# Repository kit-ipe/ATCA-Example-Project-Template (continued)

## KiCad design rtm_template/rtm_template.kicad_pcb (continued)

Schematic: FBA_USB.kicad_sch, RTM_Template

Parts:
C20: 100nF; C_0603_1608Metric; voltage 16 V
C23, C27, C29, C31: 10uF; C_1210_3225Metric; voltage 25 V; digikey# 445-3942-1-ND
C25, C28: 1uF; C_0402_1005Metric; voltage 16 V
C26, C30, C32, C35, C36, C41, C42, C43, C44, C45, C46, C47, C48, C49, C50, C51, C53, C54, C55: 100nF; C_0402_1005Metric; voltage 16 V
C33: 100nF; C_0402_1005Metric
C34, C37: 27pF; C_0402_1005Metric; voltage 50 V; digikey# 587-3745-1-ND
C38, C39, C40: 4.7uF; C_0603_1608Metric; voltage 25 V
FB1, FB2, FB3: 220 @ 100MHz; L_0603_1608Metric; digikey# 490-5225-1-ND
J8: USB_B_Micro; USB_Micro-B_Molex_47346-0001; digikey# WM17141CT-ND
J12: Conn_02x05_Odd_Even; IDC-Header_2x05_P2.54mm_Horizontal_withoutsilkscreen; mouser# 571-5103311-1; digikey# A33180-ND
R40: 1M; R_0603_1608Metric
R42, R44, R46, R48, R65, R68: 4k7; R_0402_1005Metric; tolerance 1%; digikey# A129635CT-ND
R57, R60: 33; R_0402_1005Metric; digikey# A129609CT-ND
R61, R63, R64, R70: 10k; R_0402_1005Metric; tolerance 1%; digikey# A129639CT-ND
R62, R71: 2k; R_0402_1005Metric; tolerance 1%; digikey# RMCF0402FT2K00CT-ND
R66: 12k; R_0402_1005Metric; tolerance 1%; digikey# A129640CT-ND
R67, R72: 1k; R_0402_1005Metric; tolerance 1%; digikey# A129627CT-ND
R69: DNP; R_0402_1005Metric_DNP
U8: AZ1117-3.3; SOT-223-3_TabPin2; mouser# 621-AZ1117CH-3.3TRG1; digikey# AZ1117CH-3.3TRG1DICT-ND
U9: MIC94161YCS-TR; WLCSP-6_1.0x1.5mm_P0.5mm; mouser# 998-MIC94161YCS-TR; digikey# 576-4453-1-ND
U10: USBLC6-4SC6; SOT-23-6; mouser# 511-USBLC6-4SC6Y; digikey# 497-11883-1-ND
U11: 93LC56B-MC; DFN-8-1EP_3x2mm_P0.5mm_EP1.75x1.45mm; mouser# 579-93LC56BT-I/MC; digikey# 93LC56BT-I/MCCT-ND
U12: FT4232H-56Q; VQFN-56-1EP_8x8mm_P0.5mm_EP5.9x5.9mm; mouser# 895-FT4232H-56Q-TRAY; digikey# 768-1378-1-ND
U13: TXS0104RGYR; Texas_S-PVQFN-N14; mouser# 595-TXS0104ERGYR; digikey# 296-20698-1-ND
U14: MAX9100EUK-T; SOT-23-5; mouser# 700-MAX9100EUKT; digikey# MAX9100EUK+TCT-ND
U15: SN74LVC07APW; TSSOP-14_4.4x5mm_P0.65mm; digikey# 296-26575-5-ND
Y1: ECS-120-12-36Q-CWY-TR; Crystal_SMD_2520-4Pin_2.5x2.0mm; mouser# 520-120-12-36Q-CWYT; digikey# XC2419CT-ND

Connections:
+1V8_USB_VCORE: C35.1, C36.1, C40.1, C43.1, C46.1, C48.1, U12.2 (VCORE), U12.31 (VCORE), U12.43 (VREGOUT)
+3V3_USB_VCCIO: C29.1, C32.1, C44.1, C47.1, C49.1, C50.1, C51.1, C55.1, FB2.2, FB3.2, R61.1, R63.1, R64.1, R67.2, R69.1, R71.2, U8.2 (VO), U11.8 (VCC), U12.16 (VCCIO), U12.36 (VCCIO), U12.44 (VREGIN), U12.50 (VCCIO), U13.14 (VCCB), U14.5 (V+)
+5V_USB_VBUS: C27.1, C28.1, C30.1, FB1.1, U8.3 (VI)
/FBA_USB/3V3_FT_INT: C31.1, J12.4, R42.1, R44.1, R46.1, R48.1, R65.1, U9.A1 (VOUT), U9.B1 (VOUT)
/FBA_USB/EECLK: R63.2, U11.2 (SCLK), U12.56 (EECLK)
/FBA_USB/EECS: R64.2, U11.1 (CS), U12.1 (EECS)
/FBA_USB/EEDATA: R62.1, U11.3 (DI), U12.55 (EEDATA)
/FBA_USB/EEDATA_R: R61.2, R62.2, U11.4 (DO)
/FBA_USB/FT4232_MR: U12.19 (ADBUS6), U15.3
/FBA_USB/FT4232_SRST_B: U12.20 (ADBUS7), U15.5
/FBA_USB/OSCI: C34.1, U12.3 (OSCI), Y1.3
/FBA_USB/OSCO: C37.1, U12.4 (OSCO), Y1.1
/FBA_USB/SLAVE_JTAG.TRST: J12.6, R65.2, U15.1
/FBA_USB/SRST: R68.2, U15.2, U15.6
/FBA_USB/UART0_RXD_I: U12.23 (BDBUS1), U13.12 (B2)
/FBA_USB/UART0_TXD_O: U12.22 (BDBUS0), U13.13 (B1)
/FBA_USB/UART1_RXD_I: U12.33 (CDBUS1), U13.10 (B4)
/FBA_USB/UART1_TXD_O: U12.32 (CDBUS0), U13.11 (B3)
/FBA_USB/USB_DATA_N: J8.2 (D-), R57.2, U10.1 (I/O1), U10.3 (I/O2)
/FBA_USB/USB_DATA_P: J8.3 (D+), R60.2, U10.4 (I/O3), U10.6 (I/O4)
/FBA_USB/USB_N: R57.1, U12.7 (DM)
/FBA_USB/USB_P: R60.1, U12.8 (DP)
/FBA_USB/USB_VBUS: C25.1, C33.1, FB1.2, J8.1 (VBUS), U10.5 (VBUS)
/FBA_USB/USB_VPHY: C38.1, C41.1, FB2.1, U12.5 (VPHY)
/FBA_USB/USB_VPLL: C39.1, C42.1, FB3.1, U12.9 (VPLL)
/FBA_USB/VCCO_JTAG_ON: U12.17 (ADBUS4), U14.1
GND: C20.2, C23.2, C25.2, C26.2, C27.2, C28.2, C29.2, C30.2, C31.2, C32.2, C33.2, C34.2, C35.2, C36.2, C37.2, C38.2, C39.2, C40.2, C41.2, C42.2, C43.2, C44.2, C45.2, C46.2, C47.2, C48.2, C49.2, C50.2, C51.2, C53.2, C54.2, C55.2, J8.5 (GND), J12.2, J12.10, R40.1, R66.2, R72.2, U8.1 (GND), U9.C1 (GND), U10.2 (GND), U11.5 (GND), U12.10 (TEST), U12.21 (GND), U12.41 (GND), U12.45 (GND), U12.57 (EPAD), U13.7 (GND), U13.15 (EPAD), U14.2 (V-), U15.7 (GND), U15.9, U15.11, U15.13, Y1.2, Y1.4; also elsewhere on the board
unnamed: C20.1, J8.6 (Shield), R40.2
unnamed: R66.1, U12.6 (REF)
unnamed: R67.1, U12.11 (~RESET)
unnamed: R70.1, U13.8 (OE)
unnamed: R71.1, R72.1, U14.4 (-)
Z3_1V8_STBY: C53.1, C54.1, R70.2, U13.1 (VCCA), U14.3 (+); also elsewhere on the board
Z3_3V3_STBY: C23.1, C26.1, C45.1, R68.1, U9.A2 (VIN), U9.B2 (VIN), U9.C2 (EN), U15.14 (VCC); also elsewhere on the board
Z3_MCU_JTCK-SWCLK: J12.1, R48.2, U12.12 (ADBUS0); also elsewhere on the board
Z3_MCU_JTDI: J12.9, R42.2, U12.13 (ADBUS1); also elsewhere on the board
Z3_MCU_JTDO-SWO: J12.3, R46.2, R69.2, U12.14 (ADBUS2); also elsewhere on the board
Z3_MCU_JTMS-SWDIO: J12.5, R44.2, U12.15 (ADBUS3); also elsewhere on the board
Z3_MR: U15.4; also elsewhere on the board
Z3_UART0_RX: U13.2 (A1); also elsewhere on the board
Z3_UART0_TX: U13.3 (A2); also elsewhere on the board
Z3_UART1_RX: U13.4 (A3); also elsewhere on the board
Z3_UART1_TX: U13.5 (A4); also elsewhere on the board

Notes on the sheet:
SLAVE_JTAG.TDO
SLAVE_JTAG.TDI
SLAVE_JTAG.TMS
JTAG Slave header
SLAVE_JTAG.TCK
NOTE: Chamfered pad could be pin 1 or pin 4

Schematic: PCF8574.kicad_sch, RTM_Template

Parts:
C15: 100nF; C_0402_1005Metric
D8, D9, D10, D11, D12, D13, D14, D15: GRN; APA2106x; digikey# 754-1057-1-ND
R32, R33, R34, R35, R36, R37, R38, R39: 150; R_0402_1005Metric; digikey# A129617CT-ND
U6: PCF8574PW; TSSOP-20_4.4x6.5mm_P0.65mm; mouser# 595-PCF8574PW

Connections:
+3V3: C15.1, U6.5 (VDD), U6.7 (A1); also elsewhere on the board
+5V: R32.2, R33.2, R34.2, R35.2, R36.2, R37.2, R38.2, R39.2; also elsewhere on the board
/AT24C512C/SCL: U6.2 (SCL); also elsewhere on the board
/AT24C512C/SDA: U6.4 (SDA); also elsewhere on the board
GND: C15.2, U6.6 (A0), U6.9 (A2), U6.15 (VSS); also elsewhere on the board
unnamed: D8.1 (K), U6.10 (P0)
unnamed: D8.2 (A), R32.1
unnamed: D9.1 (K), U6.11 (P1)
unnamed: D9.2 (A), R33.1
unnamed: D10.1 (K), U6.12 (P2)
unnamed: D10.2 (A), R34.1
unnamed: D11.1 (K), U6.14 (P3)
unnamed: D11.2 (A), R35.1
unnamed: D12.1 (K), U6.16 (P4)
unnamed: D12.2 (A), R36.1
unnamed: D13.1 (K), U6.17 (P5)
unnamed: D13.2 (A), R37.1
unnamed: D14.1 (K), U6.19 (P6)
unnamed: D14.2 (A), R38.1
unnamed: D15.1 (K), U6.20 (P7)
unnamed: D15.2 (A), R39.1

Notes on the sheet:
Green
Addr 0x3A = 0b011 1010
AMC_USR_LED

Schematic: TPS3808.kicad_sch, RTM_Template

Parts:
C5: 100nF; C_0402_1005Metric; voltage 25 V
R1: 51k; R_0402_1005Metric; digikey# RMCF0402FT51K0CT-ND
U2: TPS3808G33DBVT; SOT-23-6

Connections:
+3V3: C5.1, R1.2, U2.5 (SENSE), U2.6 (VDD); also elsewhere on the board
/TPS3808/LOW_VOLTAGE_POK: U2.1 (~RESET); also elsewhere on the board
GND: C5.2, U2.2 (GND); also elsewhere on the board
unnamed: R1.1, U2.4 (CT)

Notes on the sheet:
voltage low=low
SENSE voltage
open collector output
C_T = 50k pull-up -> 300 ms delay TPS3808G33 -> Sense = 3.3 V -> Threshold = 3.07V
Internal 90k pull-up in TPS3808

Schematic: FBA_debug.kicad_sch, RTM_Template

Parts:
J7: Conn_02x05_Odd_Even; IDC-Header_2x05_P2.54mm_Horizontal_withoutsilkscreen; mouser# 571-5103311-1; digikey# A33180-ND
J9: Conn_02x07_Odd_Even; PinHeader_2x07_P1.27mm_Horizontal_withoutsilkscreen; digikey# 1175-1631-ND
J10: RJ45_MAGJACK_1000BASE; RJ45_Abracon_ARJ-205_Horizontal; mouser# 815-ARJ-205; digikey# 535-13154-ND
R31, R41, R43, R45, R47: 4k7; R_0402_1005Metric_DNP; tolerance 1%; digikey# A129635CT-ND
R49: 0; R_0402_1005Metric
R50: 1k; R_0402_1005Metric; tolerance 1%; digikey# A129627CT-ND
R51: 1M; R_1206_3216Metric
R52, R53: 200; R_0402_1005Metric
SW2, SW3: PTS645VK83-2 LFS; PTS645VK83-2; digikey# CKN10950-ND

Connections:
/FBA_debug/RJ45_CHASIS: J10.10, J10.S (Shell), R51.1
GND: J7.2, J7.10, J9.5, J9.7, J9.11, J10.1, R51.2, SW2.2, SW3.2; also elsewhere on the board
unnamed: J9.3, R49.1
unnamed: J9.13, R50.2
unnamed: J10.11 (GRN_A), R53.2
unnamed: J10.13 (YLW_A), R52.1
Z3_3V3: R49.2; also elsewhere on the board
Z3_3V3_STBY: J7.4, R31.1, R41.1, R43.1, R45.1, R47.1; also elsewhere on the board
Z3_ETH_3V3: R52.2, R53.1; also elsewhere on the board
Z3_ETH_A_N: J10.3 (TRD0-); also elsewhere on the board
Z3_ETH_A_P: J10.2 (TRD0+); also elsewhere on the board
Z3_ETH_B_N: J10.5 (TRD1-); also elsewhere on the board
Z3_ETH_B_P: J10.4 (TRD1+); also elsewhere on the board
Z3_ETH_C_N: J10.7 (TRD2-); also elsewhere on the board
Z3_ETH_C_P: J10.6 (TRD2+); also elsewhere on the board
Z3_ETH_D_N: J10.9 (TRD3-); also elsewhere on the board
Z3_ETH_D_P: J10.8 (TRD3+); also elsewhere on the board
Z3_ETH_LED0: J10.14 (YLW_K); also elsewhere on the board
Z3_ETH_LED1: J10.12 (GRN_K); also elsewhere on the board
Z3_FBA_RESET: SW2.1; also elsewhere on the board
Z3_KRIA_FWUEN: SW3.1; also elsewhere on the board
Z3_MASTER_JTAG_TCK: J7.1, R31.2; also elsewhere on the board
Z3_MASTER_JTAG_TDI: J7.9, R45.2; also elsewhere on the board
Z3_MASTER_JTAG_TDO: J7.3, R41.2; also elsewhere on the board
Z3_MASTER_JTAG_TMS: J7.5, R43.2; also elsewhere on the board
Z3_MASTER_JTAG_TRST: J7.6, R47.2; also elsewhere on the board
Z3_MCU_JTCK-SWCLK: J9.6; also elsewhere on the board
Z3_MCU_JTDI: J9.10; also elsewhere on the board
Z3_MCU_JTDO-SWO: J9.8; also elsewhere on the board
Z3_MCU_JTMS-SWDIO: J9.4; also elsewhere on the board
Z3_UART0_RX: R50.1; also elsewhere on the board
Z3_UART0_TX: J9.14; also elsewhere on the board

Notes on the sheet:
STDC14
Frontpanel Pin header connector for STLINK V3 MINI
(JTAG/SWD + UART)
JTAG Master header (for AMCs RTM and KRIA)

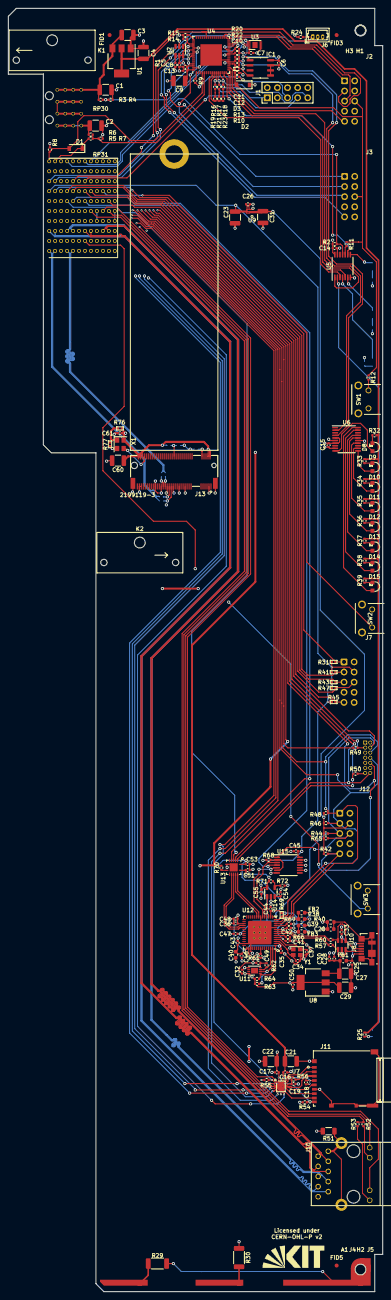
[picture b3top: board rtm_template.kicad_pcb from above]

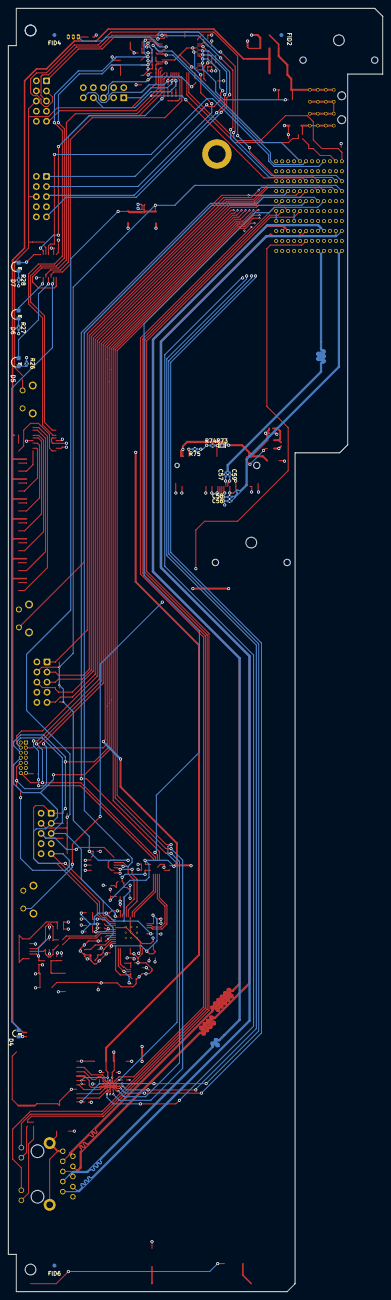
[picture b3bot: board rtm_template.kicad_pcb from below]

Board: 4 copper layers, 94.0 x 322.2 mm, 201 parts (17 on the bottom side), 163 nets.

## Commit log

2023-11-01 v1.0
